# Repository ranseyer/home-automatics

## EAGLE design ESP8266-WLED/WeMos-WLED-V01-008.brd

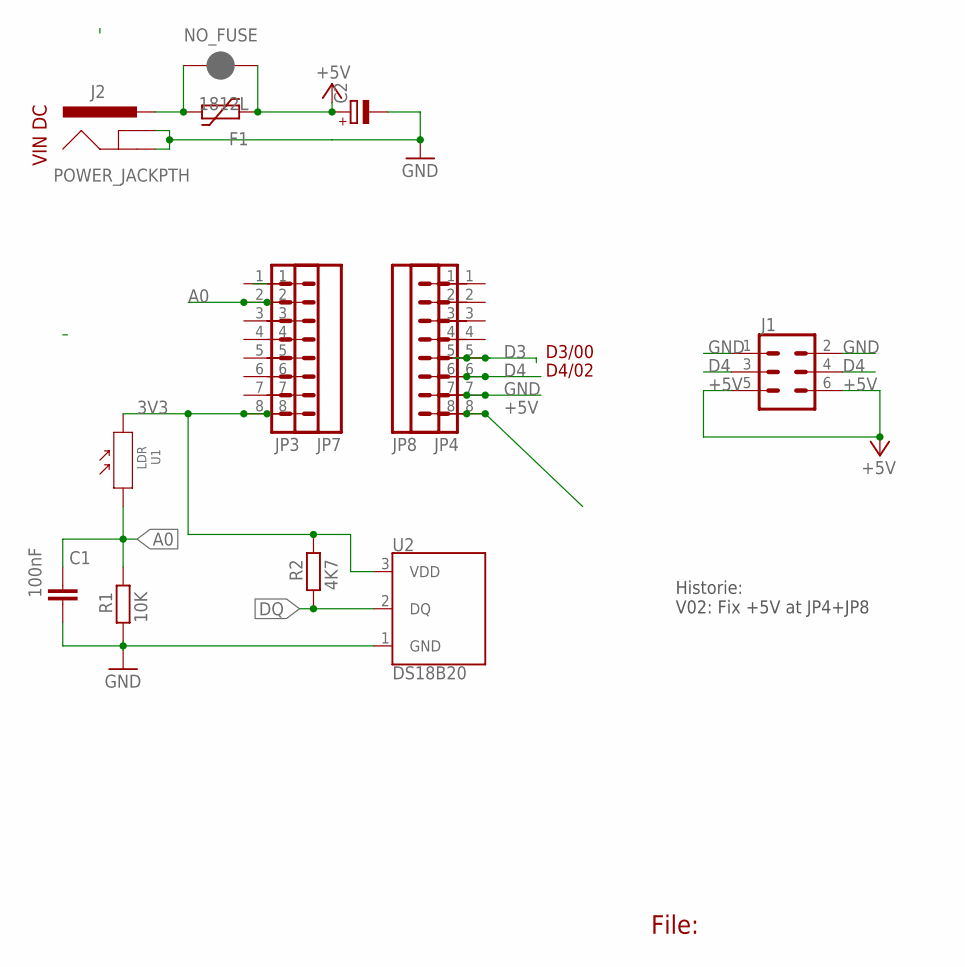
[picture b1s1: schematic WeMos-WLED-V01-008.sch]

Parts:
C1: 100nF; C0805
C2: CPOL-EUE2.5-7; E2,5-7
F1: 1812L
J1: CONN_03X22X3_SILK_MALE_PTH; 2X3
J2: POWER_JACKPTH; POWER_JACK_PTH
JP3, JP4, JP7, JP8: M08NO_SILK_FEMALE_PTH; 1X08_NO_SILK
NO_FUSE: JUMPER-SMT_2_NC_PASTE_NO-SILK; SMT-JUMPER_2_NC_PASTE_NO-SILK
R1: 10K; R0805
R2: 4K7; R0805
U1: LDR; SNR2-3.0
U2: DS18B20; TO-92-AMMO

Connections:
3V3: JP3.8, JP7.8, R2.2, U1.2, U2.3 (VDD)
+5V: C2.+, F1.P$1 (1), J1.5, J1.6, JP4.8, JP8.8, NO_FUSE.1
A0: C1.1, JP3.2, JP7.2, R1.2, U1.1
D3: JP4.5, JP8.5
D4: J1.3, J1.4, JP4.6, JP8.6
DQ: R2.1, U2.2 (DQ)
GND: C1.2, C2.-, J1.1, J1.2, J2.GND, J2.GNDBREAK, JP4.7, JP8.7, R1.1, U2.1 (GND)
RST: JP7.1
VIN: F1.P$2 (2), J2.PWR, NO_FUSE.2

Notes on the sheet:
File:
D4/02
D3/00
VIN DC
Historie: V02: Fix +5V at JP4+JP8

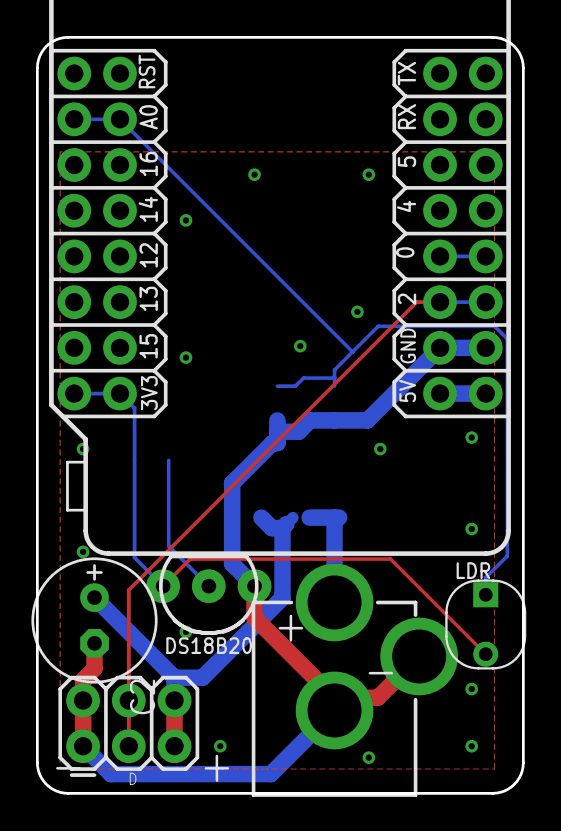
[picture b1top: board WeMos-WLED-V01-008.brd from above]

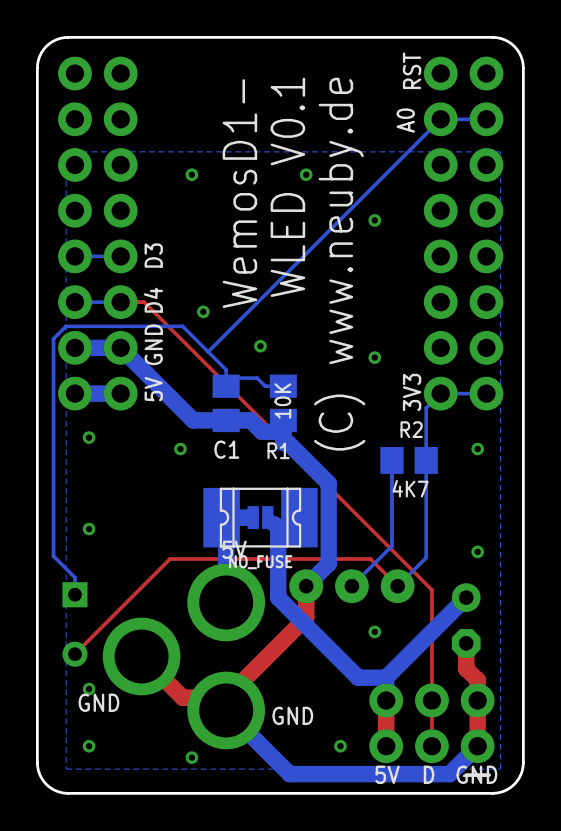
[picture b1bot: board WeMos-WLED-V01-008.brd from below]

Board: 2 copper layers, 27.0 x 42.0 mm, 14 parts (9 on the bottom side), 8 nets.

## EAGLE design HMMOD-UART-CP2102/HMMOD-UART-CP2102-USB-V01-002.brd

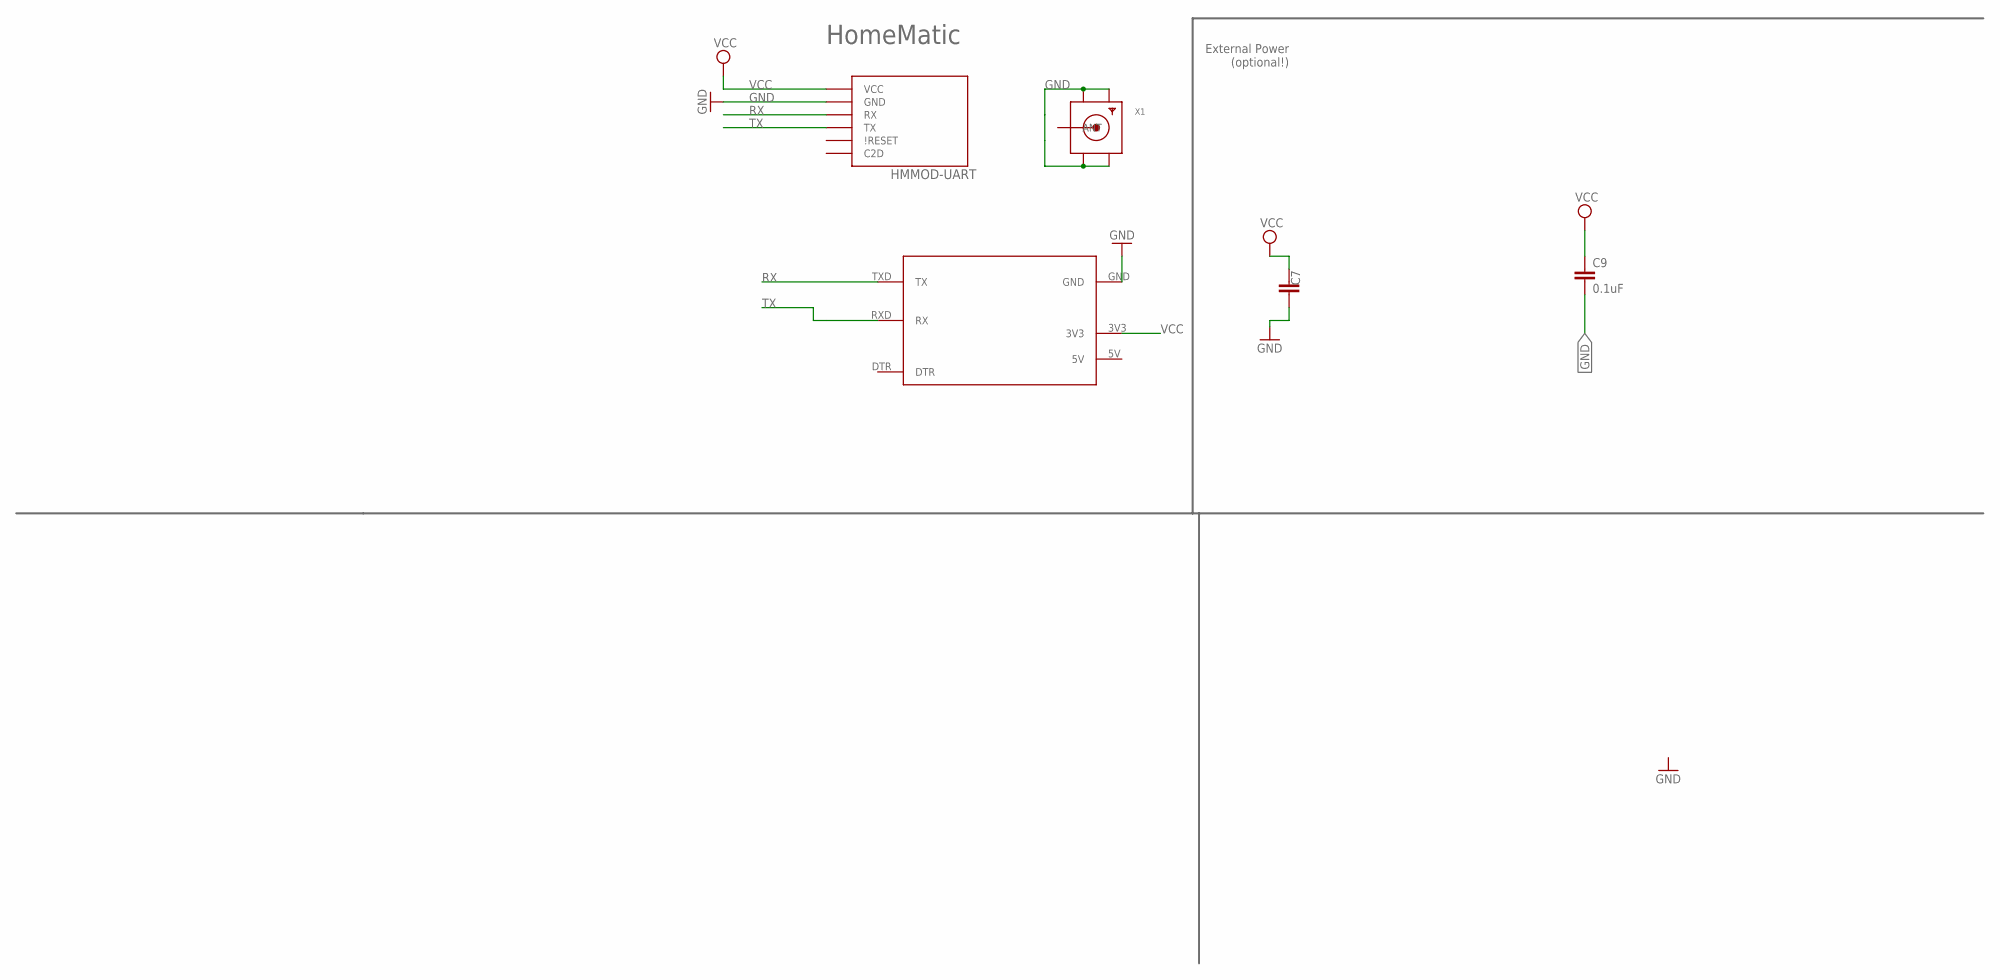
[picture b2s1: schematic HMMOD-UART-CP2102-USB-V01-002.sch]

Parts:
C7: C-EUC1812; C1812
C9: 0.1uF; C0805
HMMOD-UART: HM-MOD-UARTDIL; HM-MOD-UART-DIL
U$1: CP2101; CP2101-BEAKOUT
X1: SMACONNECTOR_EDGE; SMA_EDGELAUNCH

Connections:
5V: U$1.5V
GND: C7.1, C9.2, HMMOD-UART.2 (GND), U$1.GND, X1.GND@1 (GND4), X1.GND@2 (GND3), X1.GND@3 (GND2), X1.GND@4 (GND1)
RX: HMMOD-UART.6 (RX), U$1.TXD (TX)
TX: HMMOD-UART.5 (TX), U$1.RXD (RX)
VCC: C7.2, C9.1, HMMOD-UART.1 (VCC), U$1.3V3

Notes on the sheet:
External Power (optional!)
HomeMatic

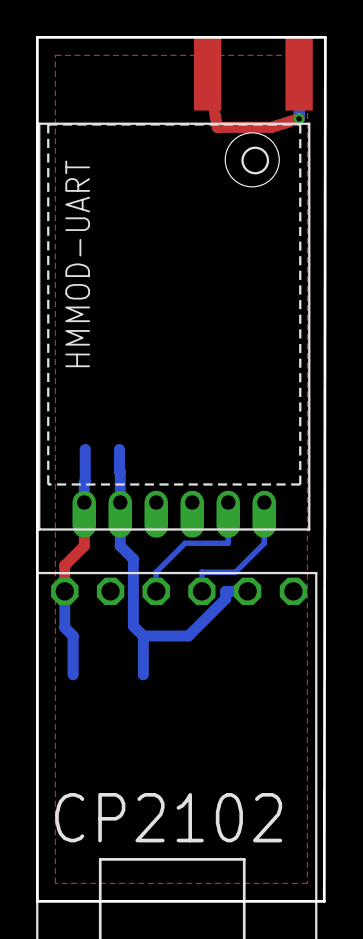
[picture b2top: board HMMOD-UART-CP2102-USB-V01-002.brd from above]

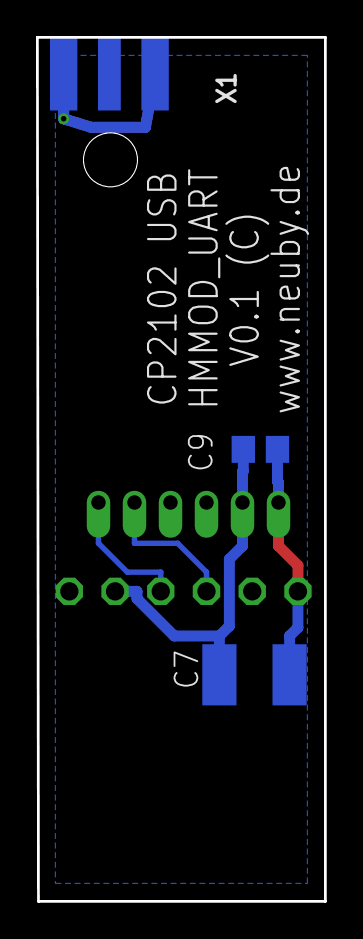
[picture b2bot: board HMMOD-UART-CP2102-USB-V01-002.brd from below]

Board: 2 copper layers, 16.0 x 48.0 mm, 5 parts (3 on the bottom side), 4 nets.

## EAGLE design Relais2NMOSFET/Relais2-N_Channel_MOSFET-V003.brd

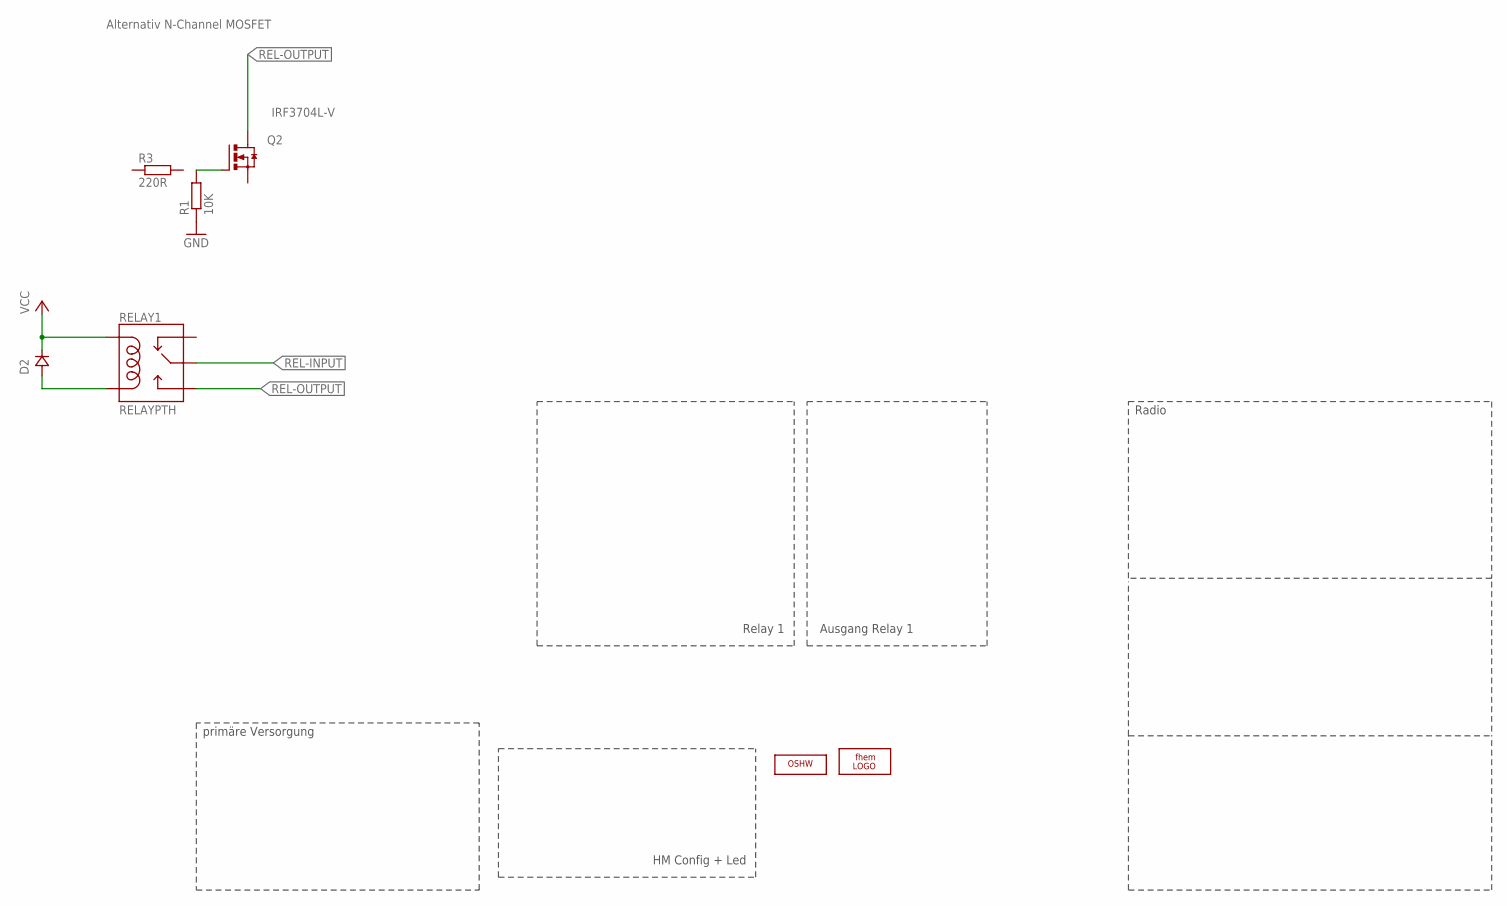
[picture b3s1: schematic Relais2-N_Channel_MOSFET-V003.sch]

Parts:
D2: SS14; DO214
LOGO2: LOGO_OSHWX0070; OSHW_6X70
Q2: IRF3704L-V; TO262-V
R1: 10K; R0805_SMALL_GAP
R3: 220R; R0805_SMALL_GAP
RELAY1: RELAYPTH; SRD-05VDC-SL-C
U$2: LOGO_FHEMSTOP; LOGO_FHEM_3X3_STOP

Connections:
GND: R1.1
unnamed: Q2.1 (G), R1.2
unnamed: D2.ANODE, RELAY1.COIL0
REL-INPUT: RELAY1.SWCOMMON
REL-OUTPUT: Q2.2 (D), RELAY1.SWOPEN
VCC: D2.CATHODE, RELAY1.COIL1

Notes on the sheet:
primäre Versorgung
Radio
HM Config + Led
Relay 1
Ausgang Relay 1
Alternativ N-Channel MOSFET

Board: 2 copper layers, 8 parts (1 on the bottom side), 4 nets, no tracks yet.

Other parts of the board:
LOGO1: LOGO_OSHWX0070; OSHW_6X70

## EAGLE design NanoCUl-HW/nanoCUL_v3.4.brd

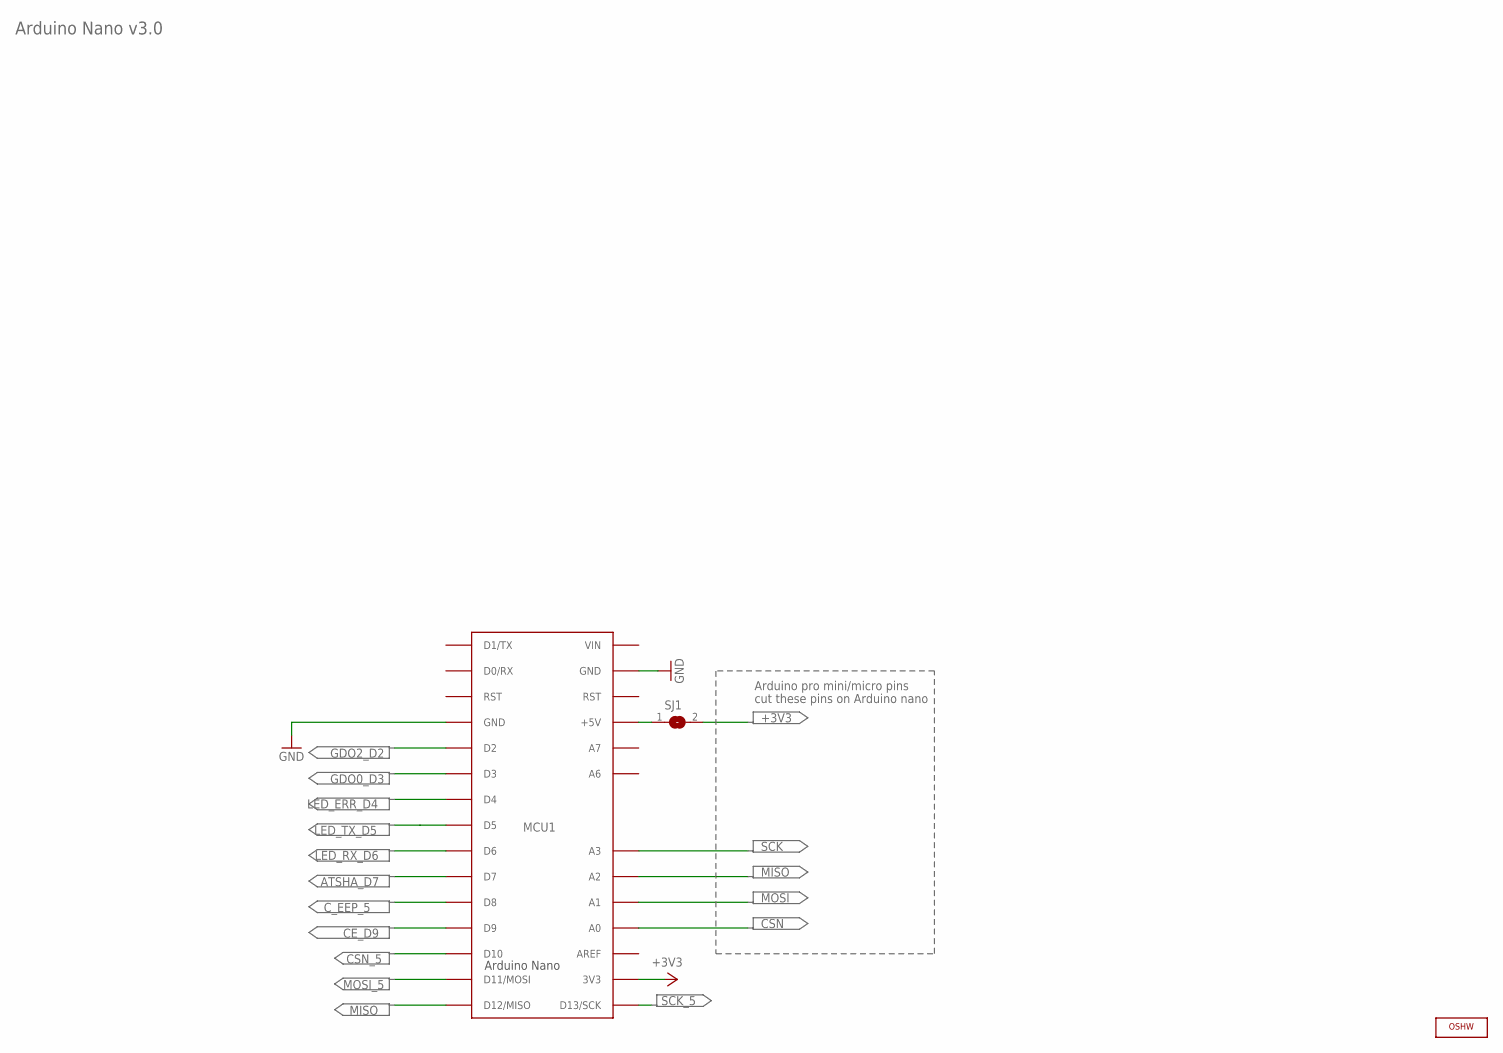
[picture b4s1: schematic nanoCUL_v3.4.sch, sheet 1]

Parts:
LOGO1: LOGO_OSHWX0070; OSHW_6X70
MCU1: ARDUINO_NANO_NO_A4-A5
SJ1: SJ

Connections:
+3V3: MCU1.3V3, SJ1.2; also elsewhere on the board
+5V: MCU1.+5V, SJ1.1
ATSHA_D7: MCU1.D7; also elsewhere on the board
CE_D9: MCU1.D9; also elsewhere on the board
CSN: MCU1.A0; also elsewhere on the board
CSN_5: MCU1.D10; also elsewhere on the board
C_EEP_5: MCU1.D8; also elsewhere on the board
GDO0_D3: MCU1.D3; also elsewhere on the board
GDO2_D2: MCU1.D2; also elsewhere on the board
GND: MCU1.GND@0 (GND), MCU1.GND@1 (GND); also elsewhere on the board
LED_ERR_D4: MCU1.D4; also elsewhere on the board
LED_RX_D6: MCU1.D6; also elsewhere on the board
LED_TX_D5: MCU1.D5; also elsewhere on the board
MISO: MCU1.A2, MCU1.D12 (D12/MISO); also elsewhere on the board
MOSI: MCU1.A1; also elsewhere on the board
MOSI_5: MCU1.D11 (D11/MOSI); also elsewhere on the board
SCK: MCU1.A3; also elsewhere on the board
SCK_5: MCU1.D13 (D13/SCK); also elsewhere on the board

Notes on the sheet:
Arduino Nano v3.0
cut these pins on Arduino nano
Arduino pro mini/micro pins

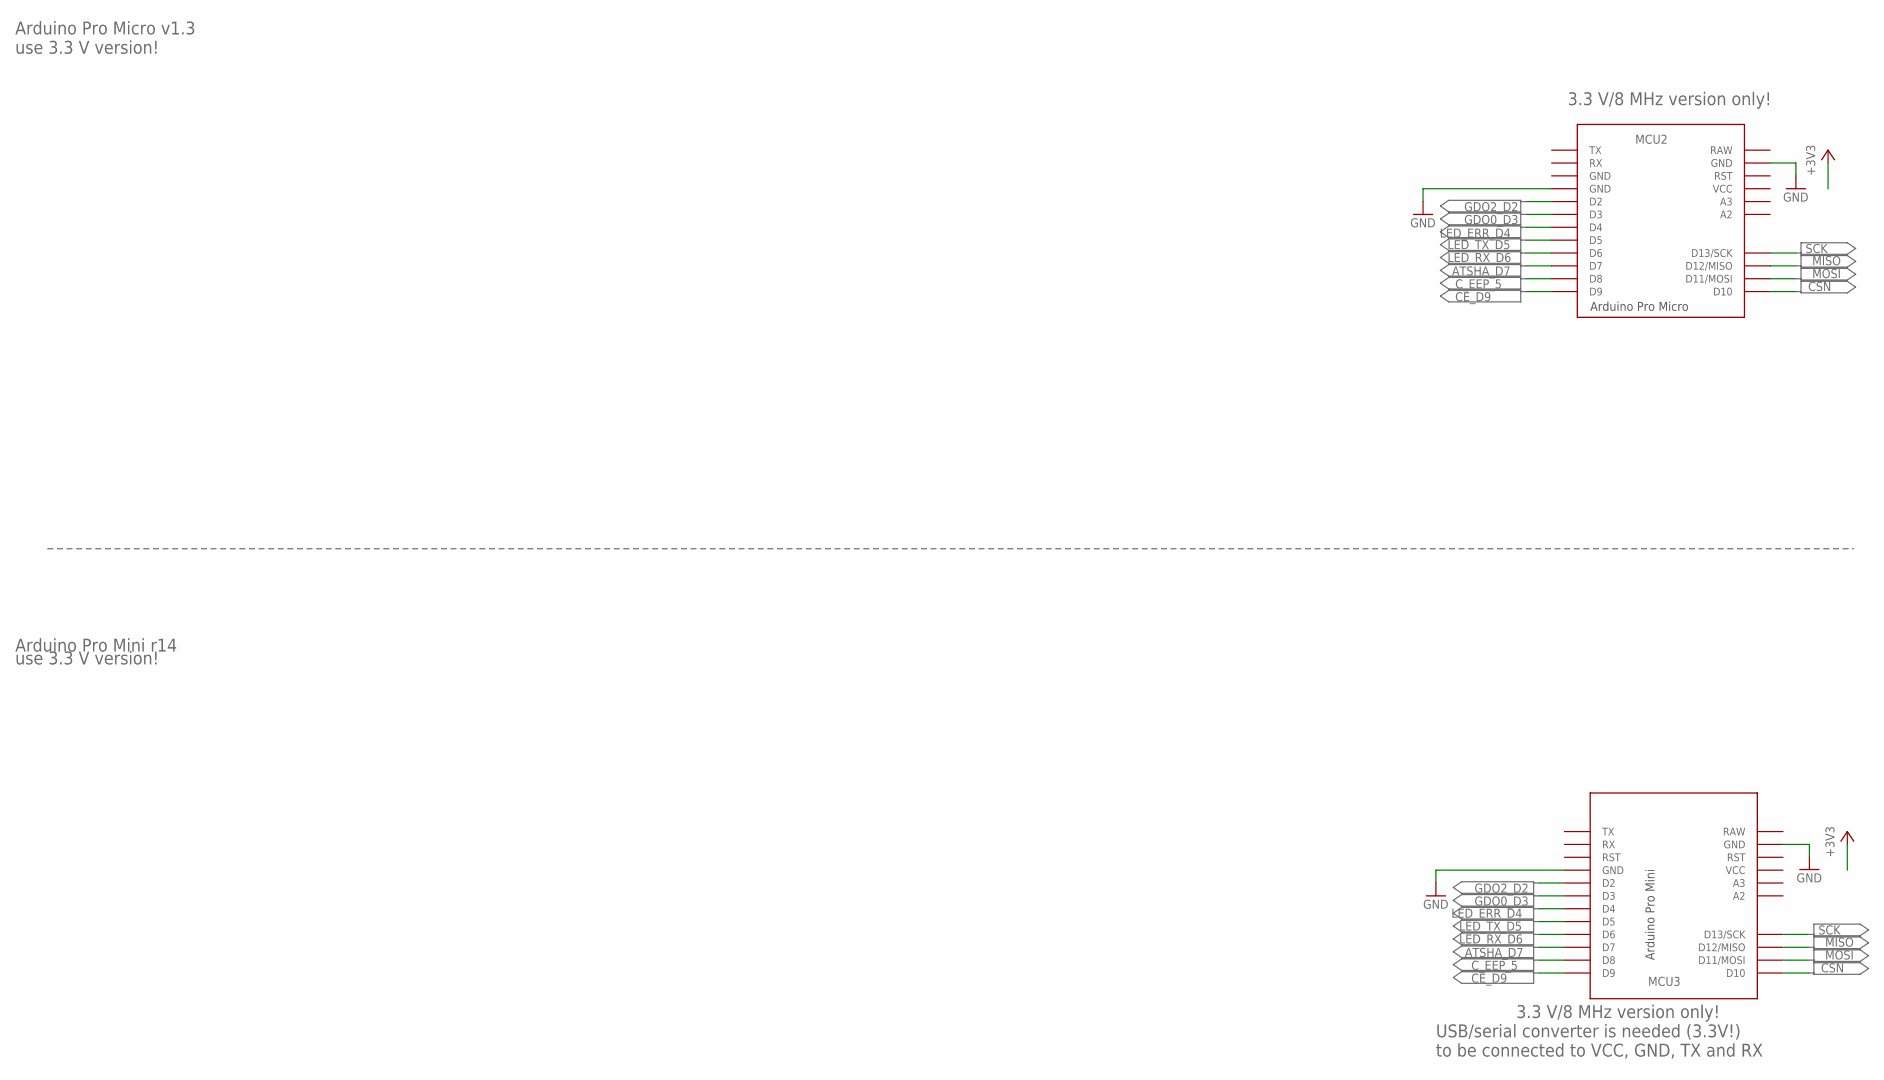
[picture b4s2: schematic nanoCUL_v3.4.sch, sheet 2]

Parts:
MCU2: ARDUINO_PRO_MICRO_NO_A0-A1
MCU3: ARDUINO_PRO_MINI_NO_A0-A1

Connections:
ATSHA_D7: MCU2.D7, MCU3.D7; also elsewhere on the board
CE_D9: MCU2.D9, MCU3.D9; also elsewhere on the board
CSN: MCU2.D10, MCU3.D10; also elsewhere on the board
C_EEP_5: MCU2.D8, MCU3.D8; also elsewhere on the board
GDO0_D3: MCU2.D3, MCU3.D3; also elsewhere on the board
GDO2_D2: MCU2.D2, MCU3.D2; also elsewhere on the board
GND: MCU2.GND@1 (GND), MCU2.GND@2 (GND), MCU3.GND@0 (GND), MCU3.GND@1 (GND); also elsewhere on the board
LED_ERR_D4: MCU2.D4, MCU3.D4; also elsewhere on the board
LED_RX_D6: MCU2.D6, MCU3.D6; also elsewhere on the board
LED_TX_D5: MCU2.D5, MCU3.D5; also elsewhere on the board
MISO: MCU2.D12/MISO, MCU3.D12/MISO; also elsewhere on the board
MOSI: MCU2.D11/MOSI, MCU3.D11/MOSI; also elsewhere on the board
SCK: MCU2.D13/SCK, MCU3.D13/SCK; also elsewhere on the board

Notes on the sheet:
Arduino Pro Micro v1.3
Arduino Pro Mini r14
use 3.3 V version!
USB/serial converter is needed (3.3V!)
to be connected to VCC, GND, TX and RX
3.3 V/8 MHz version only!

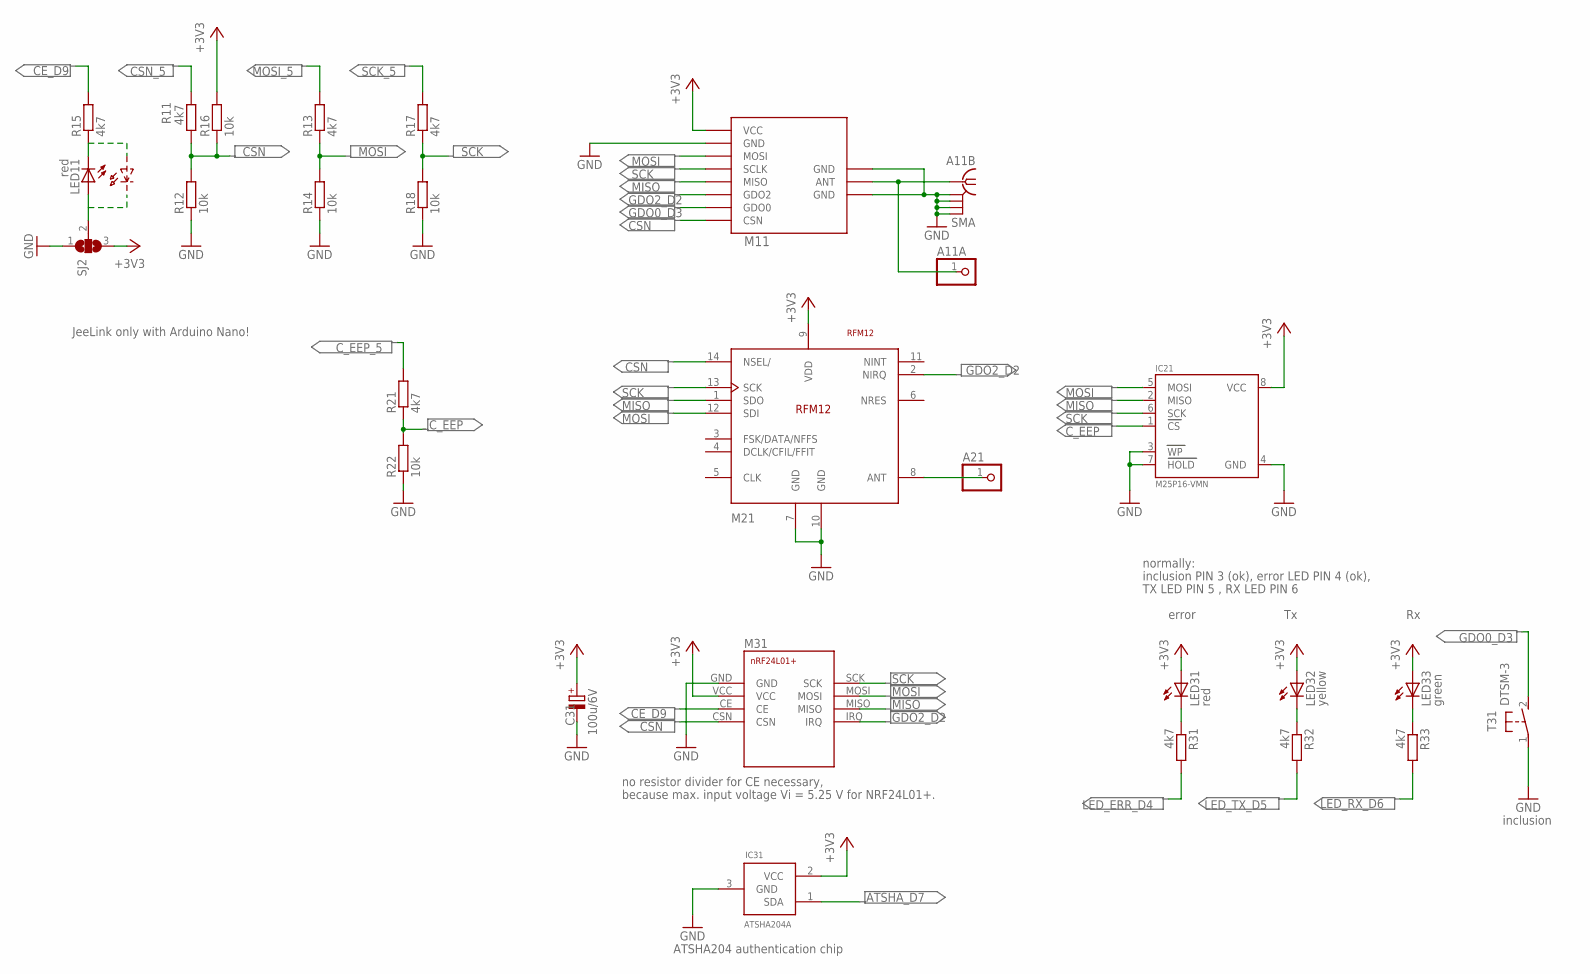
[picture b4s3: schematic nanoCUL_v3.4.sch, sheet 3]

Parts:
A11A, A21: PINHD-1X1; 1X01
A11B: SMA
C31: 100u/6V; CT3528
IC21: M25P16-VMN; SOIC8
IC31: ATSHA204A; SOT23
LED11, LED31: red; CHIPLED_1206
LED32: yellow; CHIPLED_1206
LED33: green; CHIPLED_1206
M11: CC1101_MODULE1DIL_BIG; CC1101_MODULE1_DIL-2
M21: RFM12; RFM12_SMALL
M31: NRF24L01+SMD
R11, R13, R15, R17, R21, R31, R32, R33: 4k7; R0805
R12, R14, R16, R18, R22: 10k; R0805
SJ2: SJ2W; SJ_2
T31: DTSM-3

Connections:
+3V3: C31.+, IC21.8 (VCC), IC31.2 (VCC), LED31.A, LED32.A, LED33.A, M11.1 (VCC), M21.9 (VDD), M31.VCC, R16.2, SJ2.3; also elsewhere on the board
ANT1: A11A.1, A11B.1, M11.10 (ANT)
ANT2: A21.1, M21.8 (ANT)
ATSHA_D7: IC31.1 (SDA); also elsewhere on the board
CE_D9: M31.CE, R15.2; also elsewhere on the board
CSN: M11.8 (CSN), M21.14 (NSEL/), M31.CSN, R11.1, R12.2, R16.1; also elsewhere on the board
CSN_5: R11.2; also elsewhere on the board
C_EEP: IC21.1 (CS), R21.1, R22.2
C_EEP_5: R21.2; also elsewhere on the board
GDO0_D3: M11.7 (GDO0), T31.2; also elsewhere on the board
GDO2_D2: M11.6 (GDO2), M21.2 (NIRQ), M31.IRQ; also elsewhere on the board
GND: A11B.GND@1 (2), A11B.GND@2 (3), A11B.GND@3 (4), A11B.GND@4 (5), C31.-, IC21.3 (WP), IC21.4 (GND), IC21.7 (HOLD), IC31.3 (GND), M11.2 (GND), M11.9 (GND), M11.11 (GND), M21.7 (GND), M21.10 (GND), M31.GND, R12.1, R14.1, R18.1, R22.1, SJ2.1, T31.1; also elsewhere on the board
LED_ERR_D4: R31.2; also elsewhere on the board
LED_RX_D6: R33.2; also elsewhere on the board
LED_TX_D5: R32.2; also elsewhere on the board
MISO: IC21.2 (MISO), M11.5 (MISO), M21.1 (SDO), M31.MISO; also elsewhere on the board
MOSI: IC21.5 (MOSI), M11.3 (MOSI), M21.12 (SDI), M31.MOSI, R13.1, R14.2; also elsewhere on the board
MOSI_5: R13.2; also elsewhere on the board
unnamed: LED31.C, R31.1
unnamed: LED11.C, R15.1
unnamed: LED32.C, R32.1
unnamed: LED33.C, R33.1
unnamed: LED11.A, SJ2.2
SCK: IC21.6 (SCK), M11.4 (SCLK), M21.13 (SCK), M31.SCK, R17.1, R18.2; also elsewhere on the board
SCK_5: R17.2; also elsewhere on the board

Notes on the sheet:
no resistor divider for CE necessary,
because max. input voltage Vi = 5.25 V for NRF24L01+.
JeeLink only with Arduino Nano!
error
inclusion
normally:
inclusion PIN 3 (ok), error LED PIN 4 (ok),
TX LED PIN 5 , RX LED PIN 6
ATSHA204 authentication chip

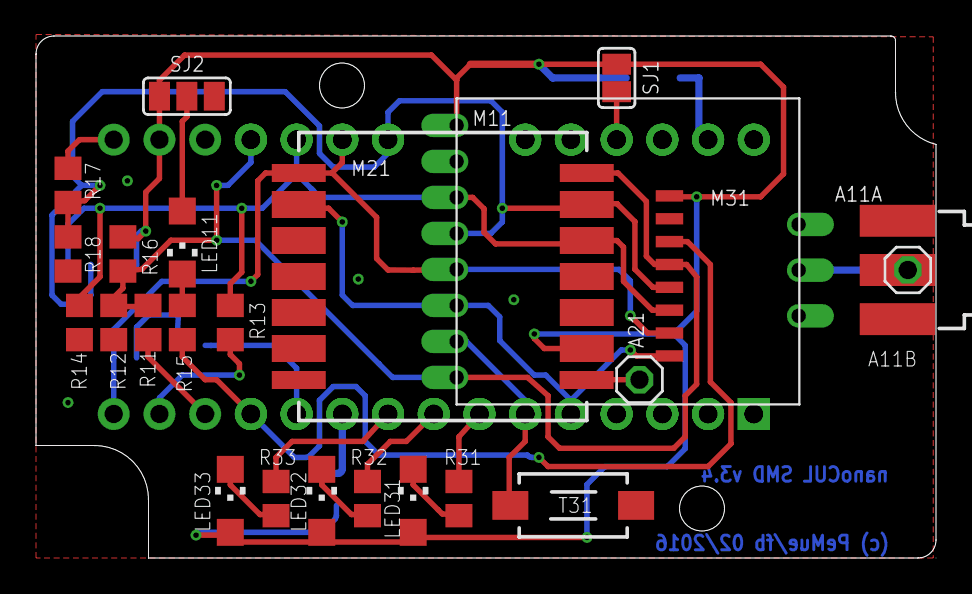
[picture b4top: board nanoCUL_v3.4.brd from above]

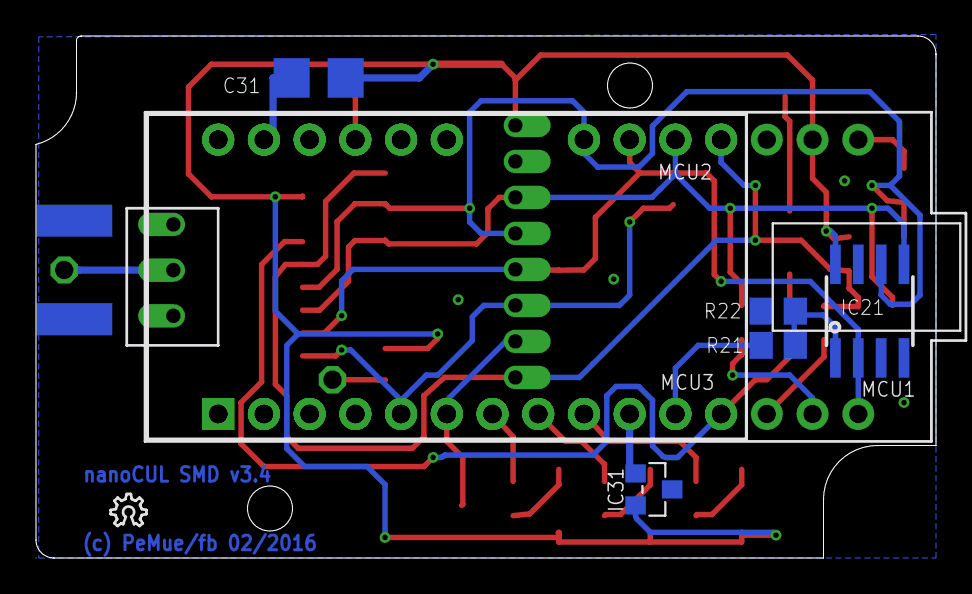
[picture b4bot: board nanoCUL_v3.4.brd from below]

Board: 2 copper layers, 50.0 x 29.0 mm, 33 parts (9 on the bottom side), 26 nets.

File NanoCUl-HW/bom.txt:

Partlist

Exported from nanoCUL_v3.4.sch at 13.04.2020 18:44

EAGLE Version 9.5.1 Copyright (c) 1988-2019 Autodesk, Inc.

Assembly variant: 

Part     Value                      Device                     Package                    Library     Sheet

A11A                                PINHD-1X1                  1X01                       pinhead     3
A11B     SMA                        SMA                        SMA                        wireless    3
A21                                 PINHD-1X1                  1X01                       pinhead     3
C31      100u/6V                    CPOL-EUCT3528              CT3528                     rcl         3
IC21     M25P16-VMN                 EEPROM_SPI_AT25040A        SOIC8                      electronics 3
IC31     ATSHA204A                  ATSHA204A                  SOT23                      Sensor      3
LED11    red                        LEDCHIPLED_1206            CHIPLED_1206               led         3
LED31    red                        LEDCHIPLED_1206            CHIPLED_1206               led         3
LED32    yellow                     LEDCHIPLED_1206            CHIPLED_1206               led         3
LED33    green                      LEDCHIPLED_1206            CHIPLED_1206               led         3
M11      CC1101_MODULE1DIL_BIG      CC1101_MODULE1DIL_BIG      CC1101_MODULE1_DIL-2       wireless    3
M21      RFM12                      RFM12SMALL                 RFM12_SMALL                wireless    3
M31      NRF24L01+SMD               NRF24L01+SMD               NRF24L01+SMD               wireless    3
MCU1     ARDUINO_NANO_NO_A4-A5      ARDUINO_NANO_NO_A4-A5      ARDUINO_NANO_NO_A4-A5      arduino     1
MCU2     ARDUINO_PRO_MICRO_NO_A0-A1 ARDUINO_PRO_MICRO_NO_A0-A1 ARDUINO_PRO_MICRO_NO_A0-A1 arduino     2
MCU3     ARDUINO_PRO_MINI_NO_A0-A1  ARDUINO_PRO_MINI_NO_A0-A1  ARDUINO_PRO_MINI_NO_A0-A1  arduino     2
R11      4k7                        R-EU_R0805                 R0805                      rcl         3
R12      10k                        R-EU_R0805                 R0805                      rcl         3
R13      4k7                        R-EU_R0805                 R0805                      rcl         3
R14      10k                        R-EU_R0805                 R0805                      rcl         3
R15      4k7                        R-EU_R0805                 R0805                      rcl         3
R16      10k                        R-EU_R0805                 R0805                      rcl         3
R17      4k7                        R-EU_R0805                 R0805                      rcl         3
R18      10k                        R-EU_R0805                 R0805                      rcl         3
R21      4k7                        R-EU_R0805                 R0805                      rcl         3
R22      10k                        R-EU_R0805                 R0805                      rcl         3
R31      4k7                        R-EU_R0805                 R0805                      rcl         3
R32      4k7                        R-EU_R0805                 R0805                      rcl         3
R33      4k7                        R-EU_R0805                 R0805                      rcl         3
SJ1                                 SJ                         SJ                         jumper      1
SJ2                                 SJ2W                       SJ_2                       jumper      3
T31      DTSM-3                     DTSM-3                     DTSM-3                     mechanics   3

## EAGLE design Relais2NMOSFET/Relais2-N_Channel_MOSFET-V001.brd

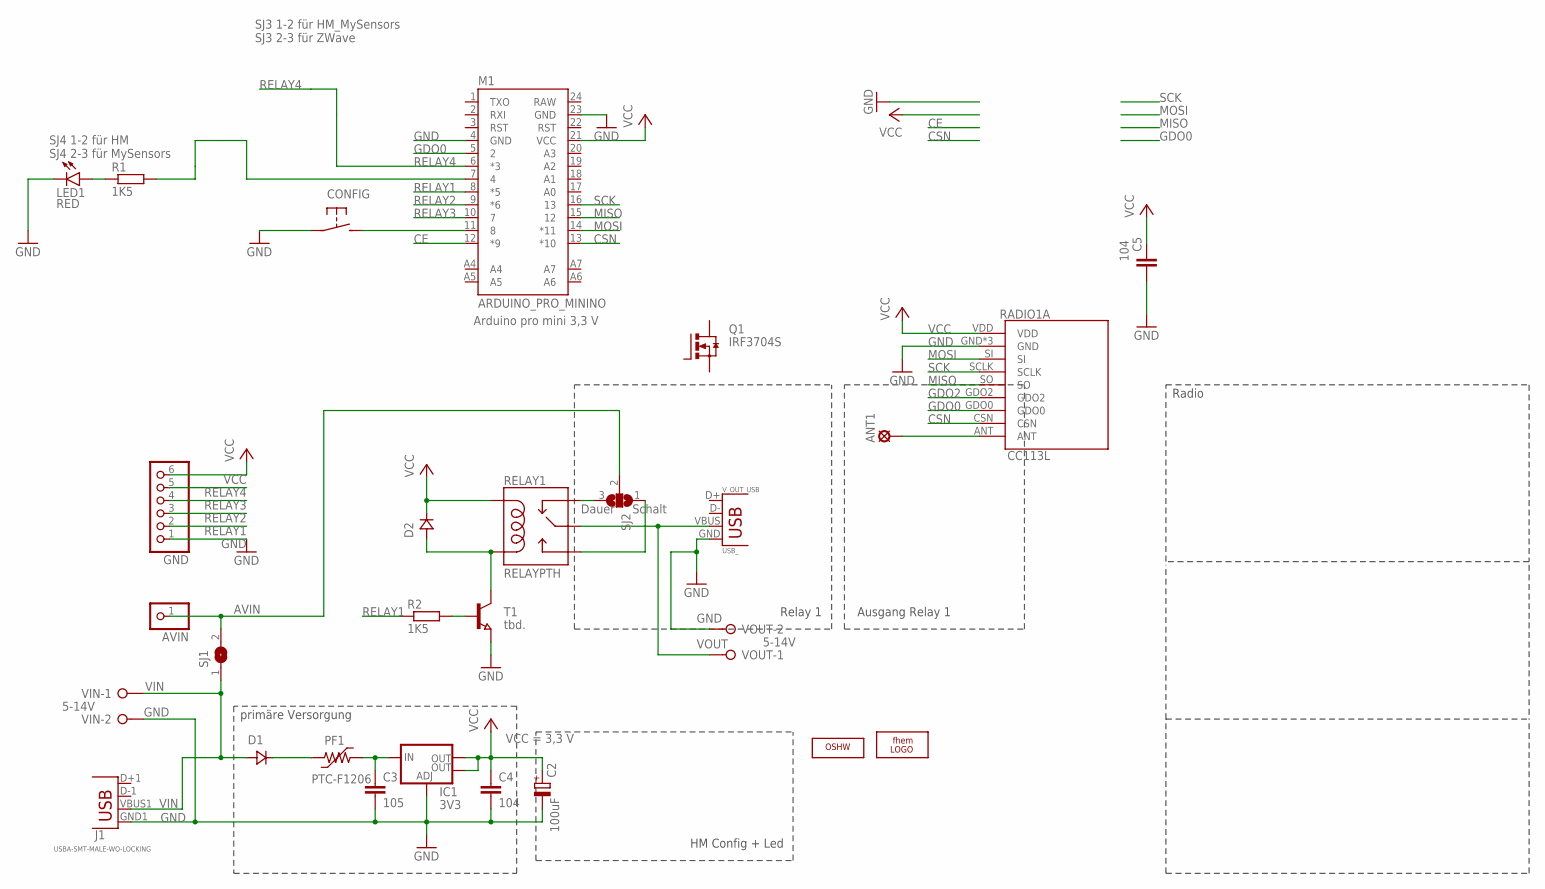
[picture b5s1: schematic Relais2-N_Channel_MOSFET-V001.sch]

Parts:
ANT1: LSP10
AVIN: PINHD-1X1; 1X01
C2: 100uF; E2,5-6E
C3: 105; C0805
C4, C5: 104; C0805
CONFIG: TASTER-SMD
D1, D2: SS14; DO214
GND: PINHD-1X6_S; 1X06
IC1: 3V3; SOT223
J1: USBA-SMT-MALE-WO-LOCKING; USB-A-SMT-MALE-NO_LOCKING
LED1: RED; LED-1206
LOGO2: LOGO_OSHWX0070; OSHW_6X70
M1: ARDUINO_PRO_MININO; ARDUINO_PRO_MINI_O
PF1: PTC-F1206; F1206
Q1: IRF3704S; D2PACK
R1, R2: 1K5; R0805_SMALL_GAP
RADIO1A: CC113L
RELAY1: RELAYPTH; SRD-05VDC-SL-C
SJ1: SJ
SJ2: SJ2W; SJ_2
T1: tbd.; SOT89
U$2: LOGO_FHEMSTOP; LOGO_FHEM_3X3_STOP
VIN: W237-132
VOUT: W237-132
V_OUT_USB: USB_; USB-A-S-SILK-FEMALE

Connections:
AVIN: AVIN.1, SJ1.2, SJ2.2
CE: M1.12 (*9)
CSN: M1.13 (*10), RADIO1A.CSN
DAUER: RELAY1.SWCLOSED (SWCLOSE), SJ2.3
GDO0: M1.5 (2), RADIO1A.GDO0
GDO2: RADIO1A.GDO2
GND: C2.-, C3.2, C4.2, C5.2, CONFIG.1, GND.1, IC1.1 (ADJ), J1.GND1 (GND), LED1.C, M1.4 (GND), M1.23 (GND), RADIO1A.GND, RADIO1A.GND1 (GND), RADIO1A.GND2 (GND), T1.3 (E), VIN.2, VOUT.2, V_OUT_USB.GND
LED: M1.7 (4), R1.2
MISO: M1.15 (12), RADIO1A.SO
MOSI: M1.14 (*11), RADIO1A.SI
unnamed: CONFIG.2 (S), M1.11 (8)
unnamed: LED1.A, R1.1
unnamed: ANT1.1, RADIO1A.ANT
unnamed: D2.ANODE, RELAY1.COIL0, T1.2 (C)
unnamed: R2.2, T1.1 (B)
RELAY1: GND.2, M1.8 (*5), R2.1
RELAY2: GND.3, M1.9 (*6)
RELAY3: GND.4, M1.10 (7)
RELAY4: GND.5, M1.6 (*3)
SCHALT: RELAY1.SWOPEN, SJ2.1
SCK: M1.16 (13), RADIO1A.SCLK
VCC: C2.+, C4.1, C5.1, D2.CATHODE, GND.6, IC1.2 (OUT), IC1.4 (OUT), M1.21 (VCC), RADIO1A.VDD, RELAY1.COIL1
VIN: D1.ANODE, J1.VBUS1 (VBUS), SJ1.1, VIN.1
VOUT: RELAY1.SWCOMMON, VOUT.1, V_OUT_USB.VBUS
VREG_IN: C3.1, IC1.3 (IN), PF1.2
VUSB: D1.CATHODE, PF1.1

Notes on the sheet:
primäre Versorgung
5-14V
Radio
HM Config + Led
Relay 1
Ausgang Relay 1
Dauer
Schalt
SJ3 1-2 für HM_MySensors SJ3 2-3 für ZWave
Arduino pro mini 3,3 V
VCC = 3,3 V
SJ4 1-2 für HM SJ4 2-3 für MySensors

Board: 2 copper layers, 29 parts (9 on the bottom side), 24 nets, no tracks yet.

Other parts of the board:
LOGO1: LOGO_OSHWX0070; OSHW_6X70

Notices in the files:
parts and their libraries:
SparkFun-Connectors: Licensing: Creative Commons ShareAlike 4.0 International - https://creativecommons.org/licenses/by-sa/4.0
polyswitch: Copyright (C) 2008, Bob Starr
